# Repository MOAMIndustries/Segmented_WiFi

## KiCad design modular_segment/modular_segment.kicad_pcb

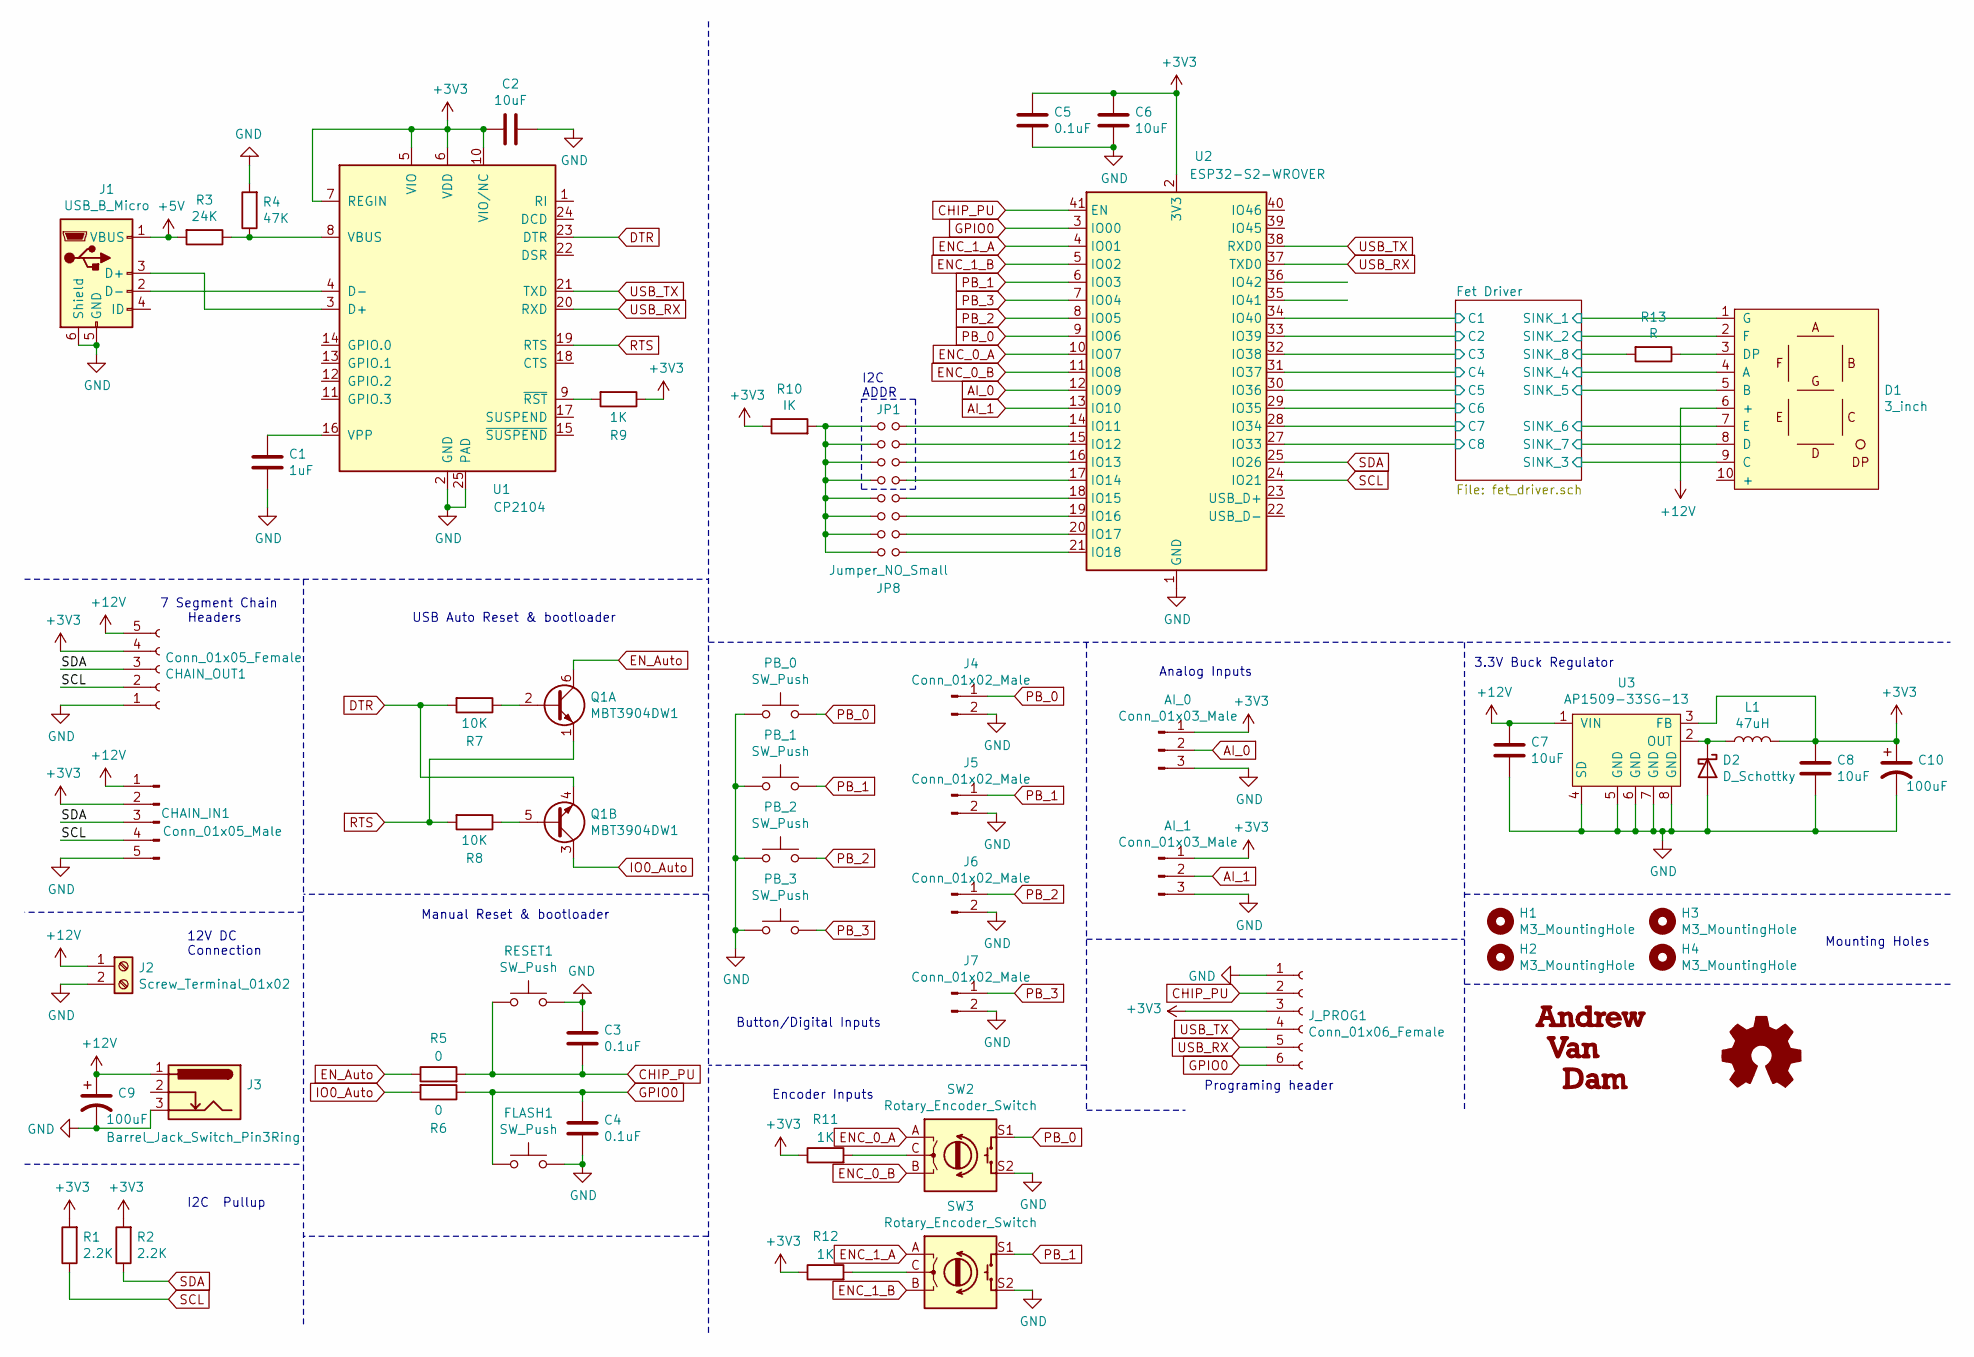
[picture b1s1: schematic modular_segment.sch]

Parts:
AI_0, AI_1: Conn_01x03_Male; PinHeader_1x03_P2.54mm_Vertical
C1: 1uF; C_0805_2012Metric_Pad1.18x1.45mm_HandSolder
C2, C6, C7, C8: 10uF; C_0805_2012Metric_Pad1.18x1.45mm_HandSolder
C3, C4, C5: 0.1uF; C_0805_2012Metric_Pad1.18x1.45mm_HandSolder
C9, C10: 100uF; CP_Radial_D8.0mm_P2.50mm; Part_No UMA1E101MDD1TP; Digikey 493-10432-1-ND
CHAIN_IN1: Conn_01x05_Male; PinHeader_1x05_P2.54mm_Horizontal
CHAIN_OUT1: Conn_01x05_Female; PinHeader_1x05_P2.54mm_Horizontal
D1: 3_inch
D2: D_Schottky; D_SMC; Part Number B340; Digikey B340-FDICT-ND
FLASH1: SW_Push; SW_SPST_PTS645
H1, H2, H3, H4: M3_MountingHole; MountingHole_3.2mm_M3_DIN965
J1: USB_B_Micro; USB_Micro-B_GCT_USB3076-30-A; Part_no USB3076-30-A; Digikey 2073-USB3076-30-ACT-ND
J2: Screw_Terminal_01x02; TerminalBlock_bornier-2_P5.08mm
J3: Barrel_Jack_Switch_Pin3Ring; BarrelJack_Wuerth_6941xx301002; Part_No 694106301002; Digikey 732-5930-ND
J4, J5, J6, J7: Conn_01x02_Male; PinHeader_1x02_P2.54mm_Vertical
JP1, JP2, JP3, JP4, JP5, JP6, JP7, JP8: Jumper_NO_Small; SolderJumper-2_P1.3mm_Open_RoundedPad1.0x1.5mm
J_PROG1: Conn_01x06_Female; PinHeader_1x06_P2.54mm_Vertical
L1: 47uH; L_12x12mm_H8mm; Part Number 7447706470; Digikey 732-7447706470CT-ND
PB_0: SW_Push; SW_Push_1P1T_NO_6x6mm_H9.5mm; Part_No 1301.9320; Digikey 486-3690-ND
PB_1, PB_2, PB_3: SW_Push; SW_Push_1P1T_NO_6x6mm_H9.5mm
Q1: MBT3904DW1; SOT-363_SC-70-6; Digikey MBT3904DW1T1GOSCT
R1, R2: 2.2K; R_0805_2012Metric_Pad1.20x1.40mm_HandSolder
R3: 24K; R_0805_2012Metric_Pad1.20x1.40mm_HandSolder
R4: 47K; R_0805_2012Metric_Pad1.20x1.40mm_HandSolder
R5, R6: 0; R_0805_2012Metric_Pad1.20x1.40mm_HandSolder
R7, R8: 10K; R_0805_2012Metric_Pad1.20x1.40mm_HandSolder
R9, R11, R12: 1K; R_0805_2012Metric_Pad1.20x1.40mm_HandSolder
R10: IK; R_0805_2012Metric_Pad1.20x1.40mm_HandSolder
R13: R; R_0805_2012Metric_Pad1.20x1.40mm_HandSolder
RESET1: SW_Push; SW_SPST_PTS645
SW2: Rotary_Encoder_Switch; RotaryEncoder_Alps_EC12E_Vertical_H20mm_CircularMountingHol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; Part_No PEC11R-4220K-S0024; Digikey PEC11R-4220K-S0024-ND
SW3: Rotary_Encoder_Switch; RotaryEncoder_Alps_EC12E_Vertical_H20mm_CircularMountingHol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
U1: CP2104; QFN-24-1EP_4x4mm_P0.5mm_EP2.6x2.6mm
U2: ESP32-S2-WROVER
U3: AP1509-33SG-13; SOP-8_3.9x4.9mm_P1.27mm; Digikey AP1509-33SGDICT-ND
g1: LOGO; Andrew_van_dam_logo_12mm

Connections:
+3V3: AI_0.1, AI_1.1, C2.1, C5.1, C6.1, C8.1, C10.1, CHAIN_IN1.2, CHAIN_OUT1.4, J_PROG1.3, L1.2, R1.2, R2.2, R9.1, R10.1, R11.1, R12.1, U1.5 (VIO), U1.6 (VDD), U1.7 (REGIN), U1.10 (VIO/NC), U2.2 (3V3), U3.3 (FB)
+5V: J1.1 (VBUS), R3.2
+12V: C7.1, C9.1, CHAIN_IN1.1, CHAIN_OUT1.5, D1.6 (+), J2.1, J3.1, U3.1 (VIN)
/Fet Driver/C1: U2.34 (IO40); also elsewhere on the board
/Fet Driver/C2: U2.33 (IO39); also elsewhere on the board
/Fet Driver/C3: U2.32 (IO38); also elsewhere on the board
/Fet Driver/C4: U2.31 (IO37); also elsewhere on the board
/Fet Driver/C5: U2.30 (IO36); also elsewhere on the board
/Fet Driver/C6: U2.29 (IO35); also elsewhere on the board
/Fet Driver/C7: U2.28 (IO34); also elsewhere on the board
/Fet Driver/C8: U2.27 (IO33); also elsewhere on the board
/Fet Driver/SINK_1: D1.1 (G); also elsewhere on the board
/Fet Driver/SINK_2: D1.2 (F); also elsewhere on the board
/Fet Driver/SINK_3: D1.9 (C); also elsewhere on the board
/Fet Driver/SINK_4: D1.4 (A); also elsewhere on the board
/Fet Driver/SINK_5: D1.5 (B); also elsewhere on the board
/Fet Driver/SINK_6: D1.7 (E); also elsewhere on the board
/Fet Driver/SINK_7: D1.8 (D); also elsewhere on the board
/Fet Driver/SINK_8: R13.2; also elsewhere on the board
AI_0: AI_0.2, U2.12 (IO09)
AI_1: AI_1.2, U2.13 (IO10)
CHIP_PU: C3.1, J_PROG1.2, R5.2, RESET1.1, U2.41 (EN)
DTR: Q1.4 (E2), R7.2, U1.23 (DTR)
ENC_0_A: SW2.A, U2.10 (IO07)
ENC_0_B: SW2.B, U2.11 (IO08)
ENC_1_A: SW3.A, U2.4 (IO01)
ENC_1_B: SW3.B, U2.5 (IO02)
EN_Auto: Q1.6 (C1), R5.1
GND: AI_0.3, AI_1.3, C1.1, C2.2, C3.2, C4.1, C5.2, C6.2, C7.2, C8.2, C9.2, C10.2, CHAIN_IN1.5, CHAIN_OUT1.1, D2.2 (A), FLASH1.2, J1.5 (GND), J1.6 (Shield), J2.2, J3.3, J4.2, J5.2, J6.2, J7.2, J_PROG1.1, PB_0.1, PB_1.1, PB_2.1, PB_3.1, R4.2, RESET1.2, SW2.S2, SW3.S2, U1.2 (GND), U1.25 (PAD), U2.1 (GND), U2.26 (GND), U2.42 (GND), U2.43 (GND), U3.4 (SD), U3.5 (GND), U3.6 (GND), U3.7 (GND), U3.8 (GND); also elsewhere on the board
GPIO0: C4.2, FLASH1.1, J_PROG1.6, R6.1, U2.3 (IO00)
IO0_Auto: Q1.3 (C2), R6.2
unnamed: C1.2, U1.16 (VPP)
unnamed: D1.3 (DP), R13.1
unnamed: D2.1 (K), L1.1, U3.2 (OUT)
unnamed: J1.2 (D-), U1.4 (D-)
unnamed: J1.3 (D+), U1.3 (D+)
unnamed: JP1.1, JP2.1, JP3.1, JP4.1, JP5.1, JP6.1, JP7.1, JP8.1, R10.2
unnamed: JP1.2, U2.14 (IO11)
unnamed: JP2.2, U2.15 (IO12)
unnamed: JP3.2, U2.16 (IO13)
unnamed: JP4.2, U2.17 (IO14)
unnamed: JP5.2, U2.18 (IO15)
unnamed: JP6.2, U2.19 (IO16)
unnamed: JP7.2, U2.20 (IO17)
unnamed: JP8.2, U2.21 (IO18)
unnamed: Q1.2 (B1), R7.1
unnamed: Q1.5 (B2), R8.1
unnamed: R3.1, R4.1, U1.8 (VBUS)
unnamed: R9.2, U1.9 (~RST)
unnamed: R11.2, SW2.C
unnamed: R12.2, SW3.C
PB_0: J4.1, PB_0.2, SW2.S1, U2.9 (IO06)
PB_1: J5.1, PB_1.2, SW3.S1, U2.6 (IO03)
PB_2: J6.1, PB_2.2, U2.8 (IO05)
PB_3: J7.1, PB_3.2, U2.7 (IO04)
RTS: Q1.1 (E1), R8.2, U1.19 (RTS)
SCL: CHAIN_IN1.4, CHAIN_OUT1.2, R1.1, U2.24 (IO21)
SDA: CHAIN_IN1.3, CHAIN_OUT1.3, R2.1, U2.25 (IO26)
USB_RX: J_PROG1.5, U1.20 (RXD), U2.37 (TXD0)
USB_TX: J_PROG1.4, U1.21 (TXD), U2.38 (RXD0)

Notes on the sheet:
Programing header
USB Auto Reset & bootloader
Manual Reset & bootloader
Analog Inputs
Button/Digital Inputs
Encoder Inputs
7 Segment Chain Headers
12V DC Connection
I2C Pullup
3.3V Buck Regulator
Mounting Holes
I2C ADDR

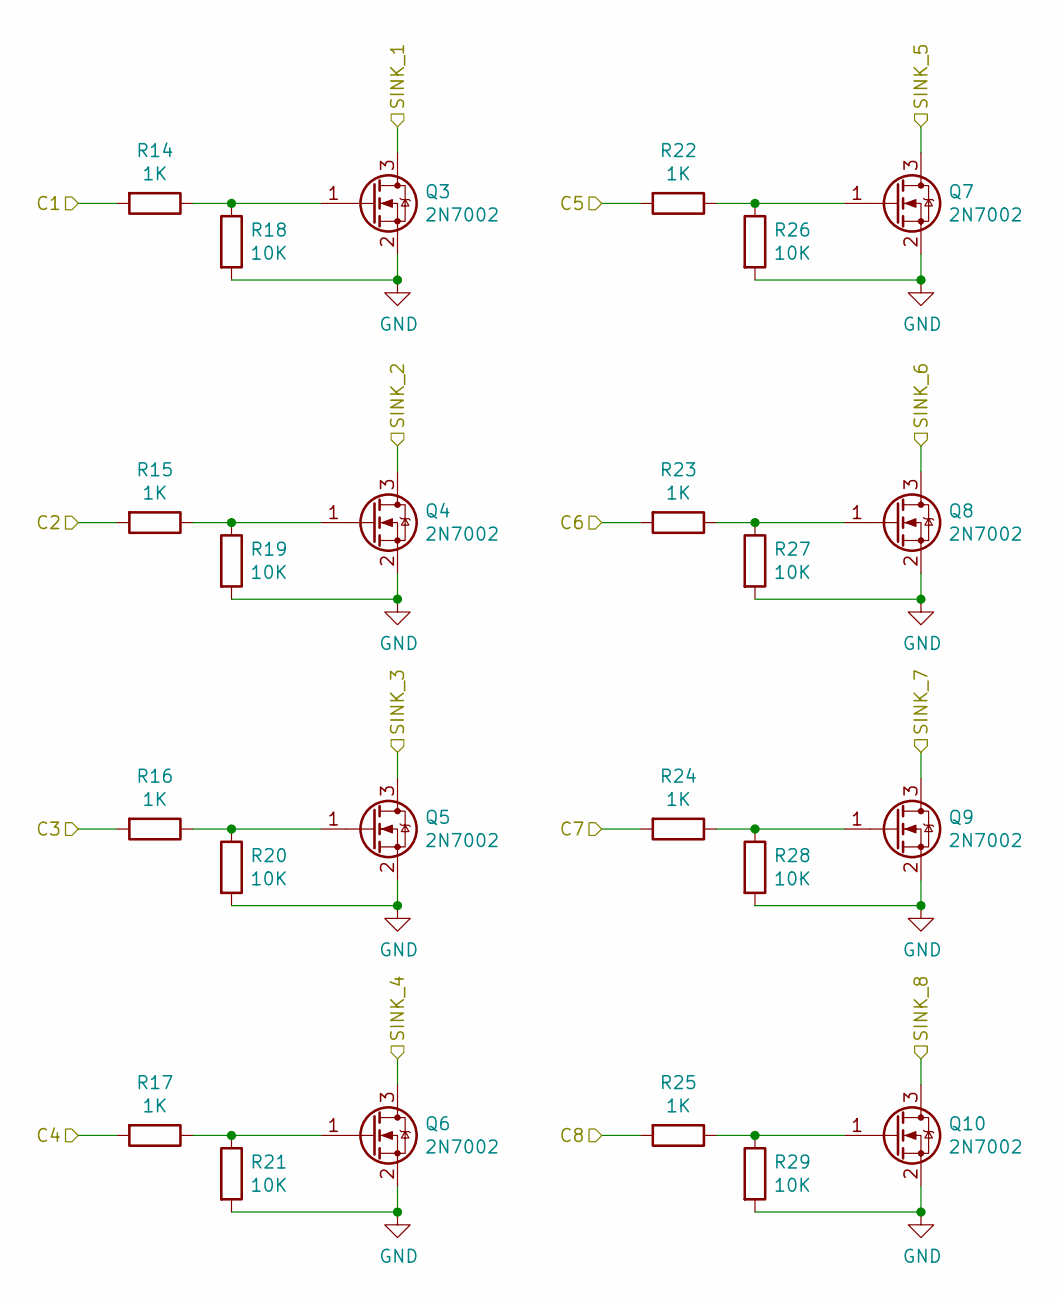
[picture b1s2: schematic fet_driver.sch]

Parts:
Q3, Q4, Q5, Q6, Q7, Q8, Q9, Q10: 2N7002; SOT-23
R14, R15, R16, R17, R22, R23, R24, R25: 1K; R_0805_2012Metric_Pad1.20x1.40mm_HandSolder
R18, R19, R20, R21, R26, R27, R28, R29: 10K; R_0805_2012Metric_Pad1.20x1.40mm_HandSolder

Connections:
/Fet Driver/C1: R14.2; also elsewhere on the board
/Fet Driver/C2: R15.2; also elsewhere on the board
/Fet Driver/C3: R16.2; also elsewhere on the board
/Fet Driver/C4: R17.2; also elsewhere on the board
/Fet Driver/C5: R22.2; also elsewhere on the board
/Fet Driver/C6: R23.2; also elsewhere on the board
/Fet Driver/C7: R24.2; also elsewhere on the board
/Fet Driver/C8: R25.2; also elsewhere on the board
/Fet Driver/SINK_1: Q3.3 (D); also elsewhere on the board
/Fet Driver/SINK_2: Q4.3 (D); also elsewhere on the board
/Fet Driver/SINK_3: Q5.3 (D); also elsewhere on the board
/Fet Driver/SINK_4: Q6.3 (D); also elsewhere on the board
/Fet Driver/SINK_5: Q7.3 (D); also elsewhere on the board
/Fet Driver/SINK_6: Q8.3 (D); also elsewhere on the board
/Fet Driver/SINK_7: Q9.3 (D); also elsewhere on the board
/Fet Driver/SINK_8: Q10.3 (D); also elsewhere on the board
GND: Q3.2 (S), Q4.2 (S), Q5.2 (S), Q6.2 (S), Q7.2 (S), Q8.2 (S), Q9.2 (S), Q10.2 (S), R18.2, R19.2, R20.2, R21.2, R26.2, R27.2, R28.2, R29.2; also elsewhere on the board
unnamed: Q3.1 (G), R14.1, R18.1
unnamed: Q4.1 (G), R15.1, R19.1
unnamed: Q5.1 (G), R16.1, R20.1
unnamed: Q6.1 (G), R17.1, R21.1
unnamed: Q7.1 (G), R22.1, R26.1
unnamed: Q8.1 (G), R23.1, R27.1
unnamed: Q9.1 (G), R24.1, R28.1
unnamed: Q10.1 (G), R25.1, R29.1

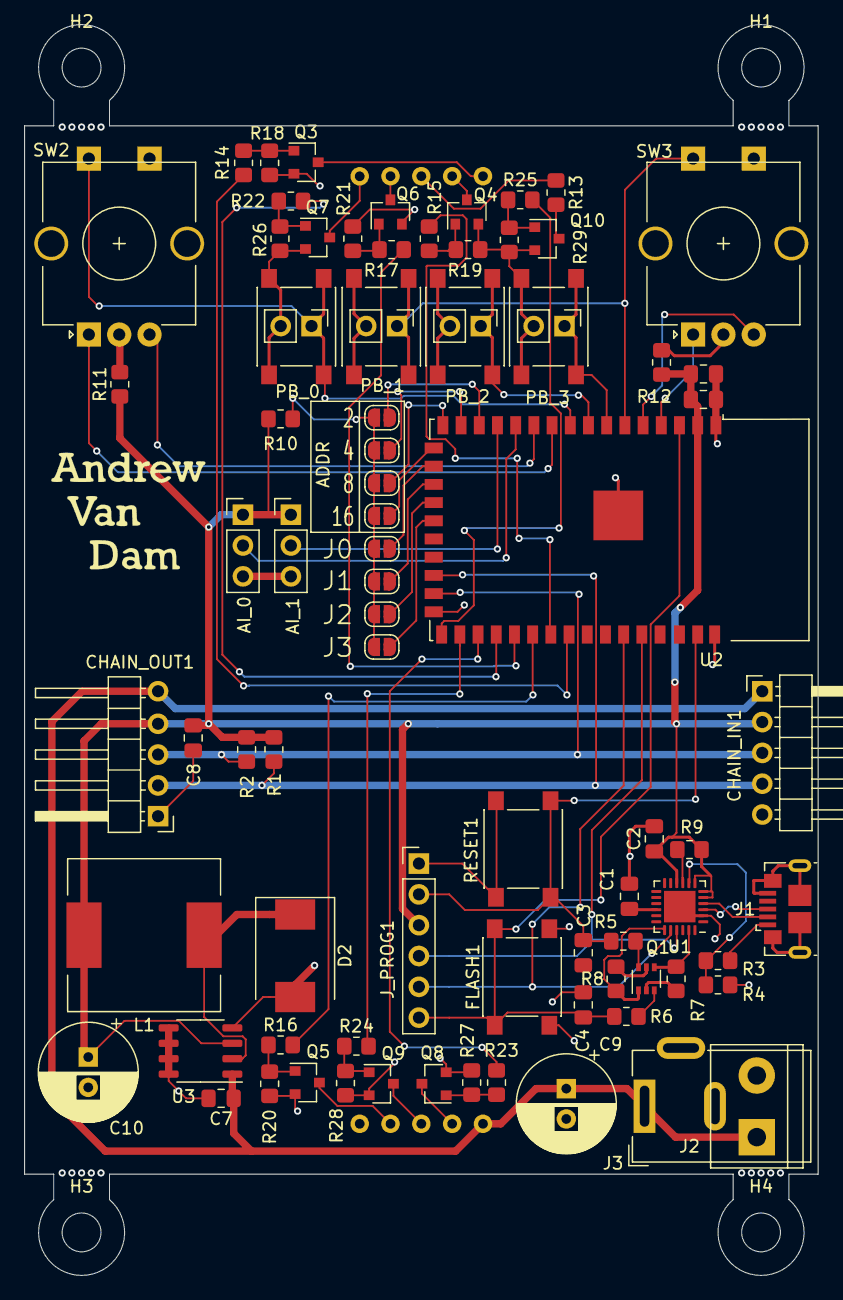
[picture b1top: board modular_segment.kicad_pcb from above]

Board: 2 copper layers, 65.4 x 103.1 mm, 87 parts (1 on the bottom side), 68 nets.

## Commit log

2021-03-27 Preliminary assembly
2021-03-28 Preliminary design complete
